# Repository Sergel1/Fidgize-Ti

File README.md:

# FIDGIEZ Ti

A programmable fidget timer built around a Raspberry Pi Pico, SSD1306 OLED display, DRV8833 motor driver, Hall effect sensor, haptic feedback and a custom-designed PCB.

## Overview

FIDGIEZ Ti combines a mechanical fidget wheel with productivity features. The device can operate as a countdown timer, focus timer, and rotation tracker. A Hall effect sensor detects wheel movement, while a 128×64 OLED provides menus, status information, RPM statistics and timer data.

## Features

- Countdown timer mode
- Focus/Pomodoro mode
- RPM measurement
- Hall sensor rotation tracking
- SSD1306 OLED interface
- Status LED
- Audible buzzer notifications
- Haptic vibration feedback
- Custom PCB designed in KiCad
- Raspberry Pi Pico based controller

## Hardware

- Raspberry Pi Pico
- SSD1306 0.96" 128×64 OLED
- DRV8833 dual motor driver
- A3144 Hall effect sensor
- Main DC motor
- Haptic vibration motor
- Passive buzzer
- LED status indicator
- 2 tactile buttons

## Schematic

## PCB Layout

## 3D PCB Render

## BOM images

## Project Status

- [x] Requirements defined
- [x] Schematic completed
- [x] PCB designed
- [x] Custom DRV8833 footprint created
- [x] Gerbers generated
- [ ] PCB ordered
- [ ] Hardware assembly
- [ ] Firmware testing
- [ ] cad files in creation few generated

## Repository Contents

```text
assets/         Images and renders
docs/           Documentation
*.*icad_pcb     PCB design
*.k*cad_sch     Schematic
BOM.csv     *   Bill of Materials
README.md    *  Project overview

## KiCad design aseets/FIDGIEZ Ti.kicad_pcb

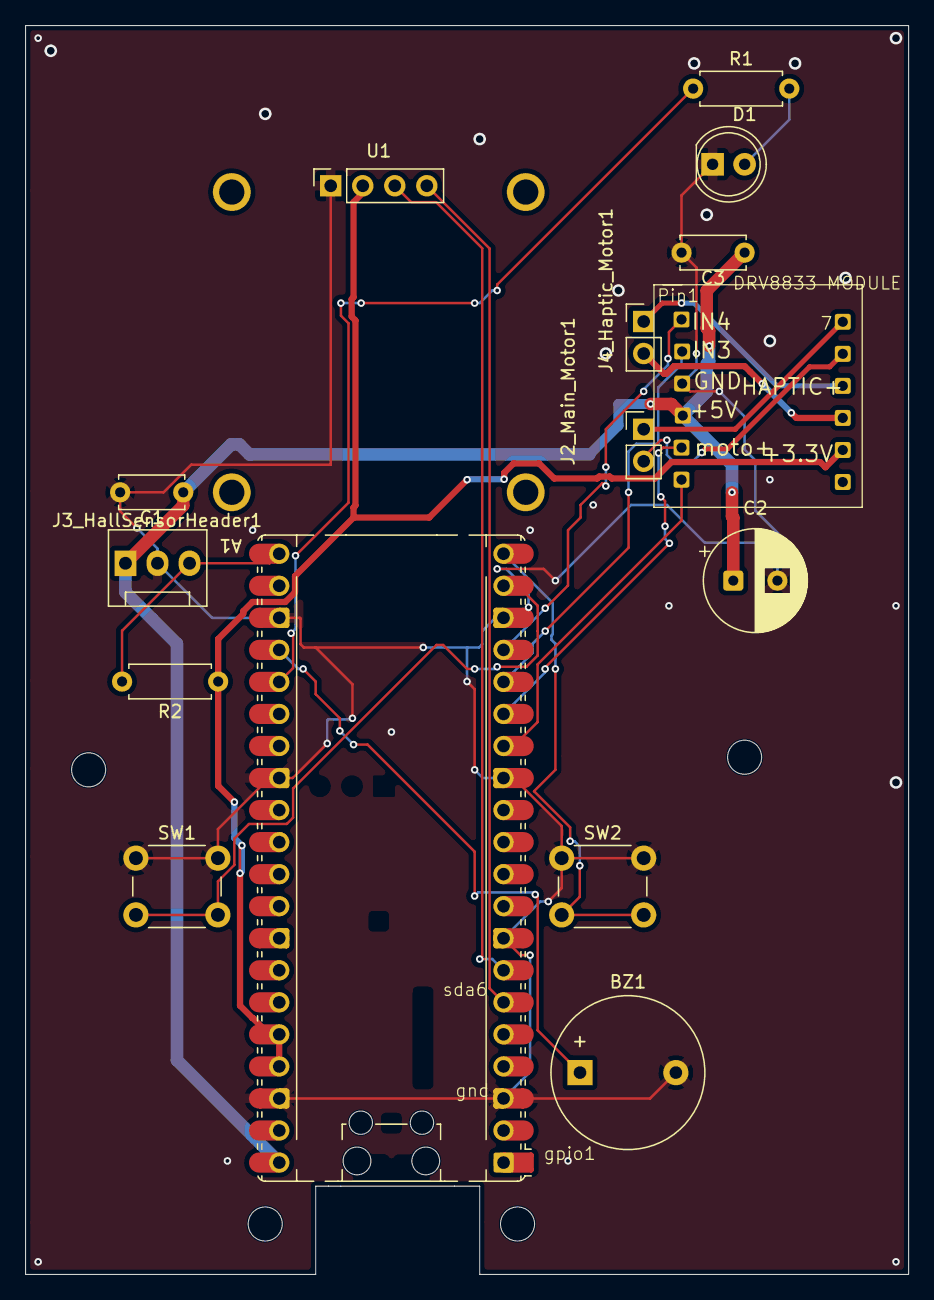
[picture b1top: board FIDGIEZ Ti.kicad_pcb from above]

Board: 2 copper layers, 70.0 x 99.0 mm, 15 parts (0 on the bottom side), 19 nets.

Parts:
A1: RaspberryPi_Pico; RaspberryPi_Pico_Common_Unspecified
BZ1: Buzzer; Buzzer_12x9.5RM7.6
C1, C3: 100nF; C_Disc_D5.0mm_W2.5mm_P5.00mm
C2: 470uF; CP_Radial_D8.0mm_P3.50mm
D1: LED; LED_D5.0mm
J2: DRV8833 connector
J2_Main_Motor1, J4_Haptic_Motor1: Conn_01x02; PinHeader_1x02_P2.54mm_Vertical
J3_HallSensorHeader1: Conn_01x03_Pin; FanPinHeader_1x03_P2.54mm_Vertical
R1: 330R; R_Axial_DIN0207_L6.3mm_D2.5mm_P7.62mm_Horizontal
R2: 10k; R_Axial_DIN0207_L6.3mm_D2.5mm_P7.62mm_Horizontal
SW1, SW2: SW_Push; SW_PUSH_6mm
U1: ER_OLEDM0.91_1x-I2C; OLED_SSD1306_I2C_0.96

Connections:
+3.3V: A1.36 (3V3), A1.37 (3V3_EN), J2.11, R2.1, U1.2 (VCC)
+5V: A1.40 (VBUS), C1.1, C2.1, C3.1, J2.4, J3_HallSensorHeader1.1
/BTN_MODE: A1.19 (GPIO14), SW1.2
/BTN_START: A1.20 (GPIO15), SW2.2
/BUZZER: A1.24 (GPIO18), BZ1.1 (+)
/HALL_SIG: A1.21 (GPIO16), J3_HallSensorHeader1.3, R2.2
/HAPTIC+: J2.9, J4_Haptic_Motor1.1
/HAPTIC-: J2.10, J4_Haptic_Motor1.2
/IN1: A1.14 (GPIO10), J2.6
/IN2: A1.15 (GPIO11), J2.5
/IN3: A1.16 (GPIO12), J2.2
/IN4: A1.17 (GPIO13), J2.1
/MOTOR_A+: J2.7, J2_Main_Motor1.1
/MOTOR_A-: J2.8, J2_Main_Motor1.2
/SCL: A1.7 (GPIO5), U1.3 (SCL)
/SDA: A1.6 (GPIO4), U1.4 (SDA)
/STATUS_LED: A1.25 (GPIO19), R1.1
GND: A1.3 (GND), A1.8 (GND), A1.13 (GND), A1.18 (GND), A1.23 (GND), A1.28 (GND), A1.38 (GND), BZ1.2 (-), C1.2, C2.2, C3.2, D1.1 (K), J2.3, J3_HallSensorHeader1.2, SW1.1, SW2.1, U1.1 (GND)
unnamed: D1.2 (A), R1.2
